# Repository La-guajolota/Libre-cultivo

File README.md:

# **Libre Cultivo 🌾**  
## 🌱 **Huerto Urbano de Precisión**  

Este repositorio contiene el desarrollo completo de un **sistema inteligente de monitoreo y control** para un huerto urbano basado en tecnologías de precisión.  
El objetivo principal es optimizar el crecimiento de cultivos hidropónicos mediante sensores, actuadores y software de automatización.  

---

## 📺 **Audiovisuales del funcionamiento**  

### **Descripción**  
¡Bienvenidos a Libre Cultivo! 🌱  

Esta playlist documenta el proceso y funcionamiento del sistema automatizado desarrollado para un huerto urbano de precisión. En los videos se exploran las siguientes áreas clave:  
- **Monitoreo en tiempo real** de parámetros como pH, temperatura, y humedad.  
- **Control automatizado** de actuadores esenciales: bombas de agua, luces LED, ventiladores y humidificadores.  
- **Interfaz gráfica** con Node-Red para una experiencia de usuario intuitiva.  
- **Almacenamiento de datos históricos** en Google Sheets, con acceso remoto y sin costo adicional.  

El contenido refleja los avances y resultados obtenidos, así como los retos superados durante la implementación de esta prueba de concepto. Es un punto de partida para futuras iteraciones hacia un sistema completamente inteligente, eficiente y accesible.  

🔗 **[Ver playlist del funcionamiento del prototipo en YouTube](https://www.youtube.com/watch?v=WTyhxuf8L80&t=177s)**  

---

### **Estructura del Sistema**  

<div align="center">
    
</div>  

El diagrama eléctrico muestra la configuración de los componentes principales del sistema:  

- **Actuadores (6 en total):**
  - **Bombas (3):**  
    - Dos bombas dosifican nutrientes al tanque con la solución general.  
    - La tercera bomba extrae esta solución para regar las plantas.  
  - **Ventiladores (2):** Regulan la temperatura dentro del rack.  
  - **Luces LED (1):** Proveen iluminación adecuada para el crecimiento de las plantas.

- **Sensores (3 en total):**  
  - **BME680:** Monitorea la temperatura y humedad en el ambiente del rack.  
  - **Sensor de temperatura:** Mide la temperatura del líquido en el tanque de la solución general.  
  - **Sensor de pH:** Verifica el nivel de pH de la solución en el tanque.  

Esta configuración permite un control preciso del microclima y los parámetros hídricos necesarios para el óptimo desarrollo de las plantas.  

---

## 🚀 **Funcionalidades**  

- **Monitoreo en tiempo real** de parámetros clave:
  - pH del agua
  - Temperatura del agua y del ambiente
  - Conductividad eléctrica (EC) *(AÚN NO AGREGADO)*
  - Sólidos disueltos totales (TDS) *(AÚN NO AGREGADO)*
  - Humedad relativa
- **Control automatizado** de:
  - Bombas de agua
  - Dosificadores de nutrientes 
  - Sistemas de iluminación LED para crecimiento
  - Ventiladores y humidificador
- **Interfaz gráfica** en Node-Red para visualización y configuración del sistema.
- **Almacenamiento de históricos**: Datos registrados en Google Sheets.
- **Control móvil**: Comunicación con el cultivo desde la aplicación gratuita MQTT Cliente.  

---

## 🛠️ **Tecnologías Utilizadas**  

### **Hardware**
- **Sensores**: DS1820, pH módulo, DHT22, BMP280
- **Microcontroladores**: ESP32 / STM32
- **Actuadores**: Bombas peristálticas, relés, ventiladores
- **Circuitos**: Diseño y fabricación de PCBs personalizados
- **PCB**: Kicad  

### **Software**
- **Lado embebido**:
  - Lenguajes: C/C++
  - Frameworks: FreeRTOS, PlatformIO, Arduino, STM32, LVGL
- **Interfaz de usuario**:
  - Lenguajes: Python
  - Frameworks: Node-RED, MQTT
- **Almacenamiento**: Google Sheets para registro histórico  

---

## 📁 **Estructura del Repositorio**  

```plaintext
.
├── hardware/            
│   ├── Actuadores/       # Esquemas eléctricos relacionados con actuadores (bombas, ventiladores, LEDs)
│   ├── Rack0/            # Diseños de PCBs y conexiones para el rack principal
│   ├── Sensores/         # Esquemas eléctricos y configuraciones de sensores utilizados
│   └── Simulaciones/     # Simulaciones de circuitos y pruebas virtuales
├── software/            
│   ├── blackpill_sensors/  # Código específico para sensores en la Blackpill
│   ├── bluepill_actuadores/ # Código para control de actuadores con la Bluepill
│   ├── Ejemplo_externos/   # Ejemplos de integración con librerías externas
│   ├── espressif/          # Código relacionado con el ESP32
│   ├── GUI/                # Interfaz gráfica para monitoreo y control
│   ├── mqttESP32/          # Implementación de MQTT para el ESP32
│   └── Python_desktop/     # Aplicaciones de escritorio en Python para control y monitoreo
├── LICENSE/               # Licencia del proyecto
└── README.md              # Descripción del proyecto

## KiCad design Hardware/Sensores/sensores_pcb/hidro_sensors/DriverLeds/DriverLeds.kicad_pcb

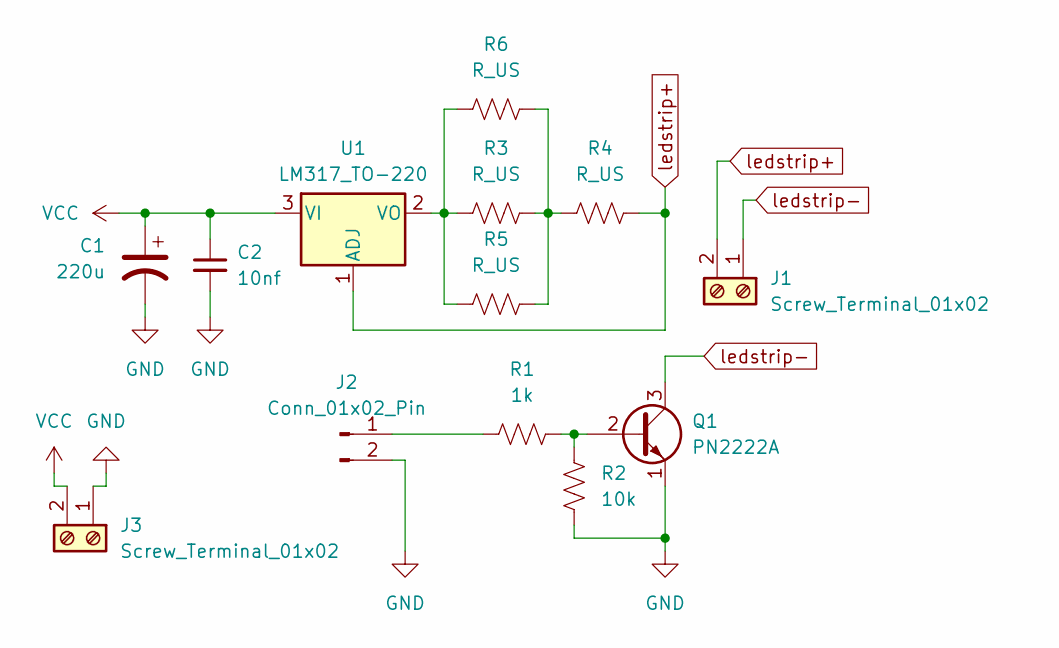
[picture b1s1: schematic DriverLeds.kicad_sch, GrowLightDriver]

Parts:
C1: 220u; CP_Radial_D12.5mm_P7.50mm
C2: 10nf; C_Axial_L5.1mm_D3.1mm_P10.00mm_Horizontal
J1, J3: Screw_Terminal_01x02; TerminalBlock_Xinya_XY308-2.54-2P_1x02_P2.54mm_Horizontal
J2: Conn_01x02_Pin; PinHeader_1x02_P2.54mm_Horizontal
Q1: PN2222A; TO-92_Inline
R1: 1k; R_Axial_DIN0207_L6.3mm_D2.5mm_P10.16mm_Horizontal
R2: 10k; R_Axial_DIN0207_L6.3mm_D2.5mm_P10.16mm_Horizontal
R3, R4, R5, R6: R_US; R_Axial_DIN0411_L9.9mm_D3.6mm_P7.62mm_Vertical
U1: LM317_TO-220; TO-220-3_Horizontal_TabDown

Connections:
GND: C1.2, C2.2, J2.2, J3.1, Q1.1 (E), R2.2
unnamed: J2.1, R1.1
unnamed: Q1.2 (B), R1.2, R2.1
unnamed: R3.1, R4.2, R5.1, R6.1
unnamed: R3.2, R5.2, R6.2, U1.2 (VO)
VCC: C1.1, C2.1, J3.2, U1.3 (VI)
ledstrip+: J1.2, R4.1, U1.1 (ADJ)
ledstrip-: J1.1, Q1.3 (C)

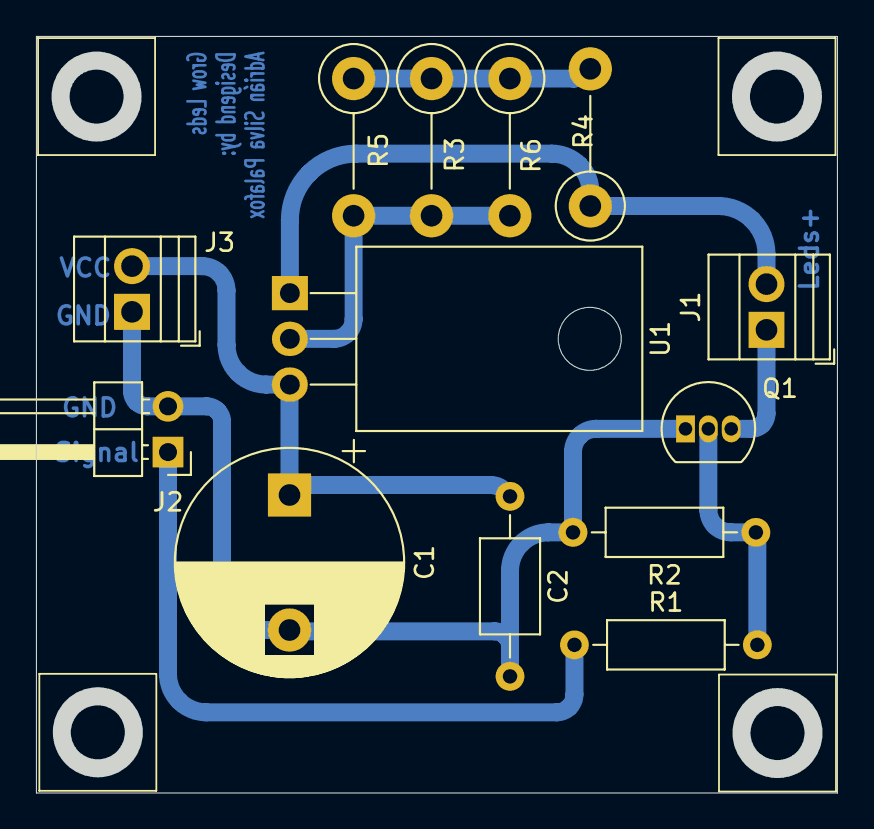
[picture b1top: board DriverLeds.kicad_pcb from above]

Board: 2 copper layers, 43.6 x 41.1 mm, 13 parts (0 on the bottom side), 8 nets.

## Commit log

2024-12-02 Primer commit de Hidroponia Colectiva
2024-12-03 Esquemas
2024-12-03 IntrumentalizacionVirtual
2024-12-07 doxeada
2024-12-20 Nuevo inicio limpio sin historial
